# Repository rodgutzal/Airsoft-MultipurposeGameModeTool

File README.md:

# Airsoft-MultipurposeGameModeTool

Herramienta multipropósito para partidas de airsoft, con hardware y software propios. Un mismo dispositivo cubre cinco modos de juego: captura la bandera, control de zona, rey de la colina, desactivación de bomba y extracción de paquete.

## Estructura

| Carpeta | Contenido |
| --- | --- |
| `Hw` | Hardware: esquemático en KiCad, PDF, lista de materiales, asignación de pines y propuesta de PCB (`Hw/pcb`). |
| `Sw` | Firmware en ESP-IDF, con su documentación. |

## Estado

Hardware en versión 0.8, en [`Hw/esquematico_v1`](Hw/esquematico_v1/README.md). Usa un ESP32-S3-DevKitC-1 N16R8 con pantalla TFT de 3.5 pulgadas (480x320, bus paralelo de 16 bits y touch resistivo XPT2046 por SPI), un expansor I2C MCP23017 para el teclado 4x4, dos switches y un push button, dos tiras LED RGB direccionables WS2812B, y audio por I2S con un amplificador MAX98357A y una bocina de 4 Ω. La alimentación tiene dos opciones y se construye una sola: un módulo LUORNG V8 para dos celdas 18650 (opción A) o TP4056 con MT3608 discretos (opción B). Todas las entradas digitales tienen pull-up externo de 10k.

La opción C (v0.9, en [`Hw/esquematico_v1/opcion_c`](Hw/esquematico_v1/opcion_c/README.md)) quita los módulos comprados para armar todo en una PCB propia: módulo ESP32-S3-WROOM-1 N16R8 sin tarjeta de desarrollo, cargador TP4056 con protección DW01A y FS8205A, elevador TPS61022, regulador AP7361C, MAX98357A suelto y USB-C al USB nativo para grabar, depurar y cargar.

El firmware está en `Sw` (ESP-IDF). Hoy arranca, fija el CPU a 240 MHz, inicia la flash y un ciclo principal de 5 ms con un LED de heartbeat; pantalla, audio, tiras LED, teclado y entradas todavía no tienen driver, y nada se ha probado en la placa. Su pinout es el de v0.7 y falta migrarlo a v0.8 (ver [`Sw/MapaPines.md`](Sw/MapaPines.md)).

## Documentación

Dónde leer según lo que necesites:

| Si quieres... | Lee |
| --- | --- |
| Entender el hardware y su pinout | [`Hw/esquematico_v1/README.md`](Hw/esquematico_v1/README.md) |
| Ver la variante para PCB propia | [`Hw/esquematico_v1/opcion_c/README.md`](Hw/esquematico_v1/opcion_c/README.md) y [`Hw/pcb/pcb_propuesta_v0.3.md`](Hw/pcb/pcb_propuesta_v0.3.md) |
| Entender cómo está organizado el firmware | [`Sw/README.md`](Sw/README.md) |
| Trabajar en el firmware (reglas, flujo de Git, cómo agregar un driver) | [`Sw/GuiaDesarrollo.md`](Sw/GuiaDesarrollo.md) |
| Saber qué hace cada función de cada driver | [`Sw/ReferenciaApi.md`](Sw/ReferenciaApi.md) |
| Saber qué pin del micro hace qué | [`Sw/MapaPines.md`](Sw/MapaPines.md) |
| Conocer el diseño objetivo del firmware | [`Sw/Arquitectura.md`](Sw/Arquitectura.md) |
| Ver el uso de memoria y los warnings | [`Sw/MemoryUsage.md`](Sw/MemoryUsage.md) y [`Sw/Warnings.md`](Sw/Warnings.md) |

## Requisitos de diseño

La autonomía mínima es de 5 horas, en periodos de uso de unos 30 minutos. El audio debe oírse a 15 metros al aire libre. El microcontrolador debe poder comprarse fácilmente en México y los precios se calculan en pesos mexicanos.

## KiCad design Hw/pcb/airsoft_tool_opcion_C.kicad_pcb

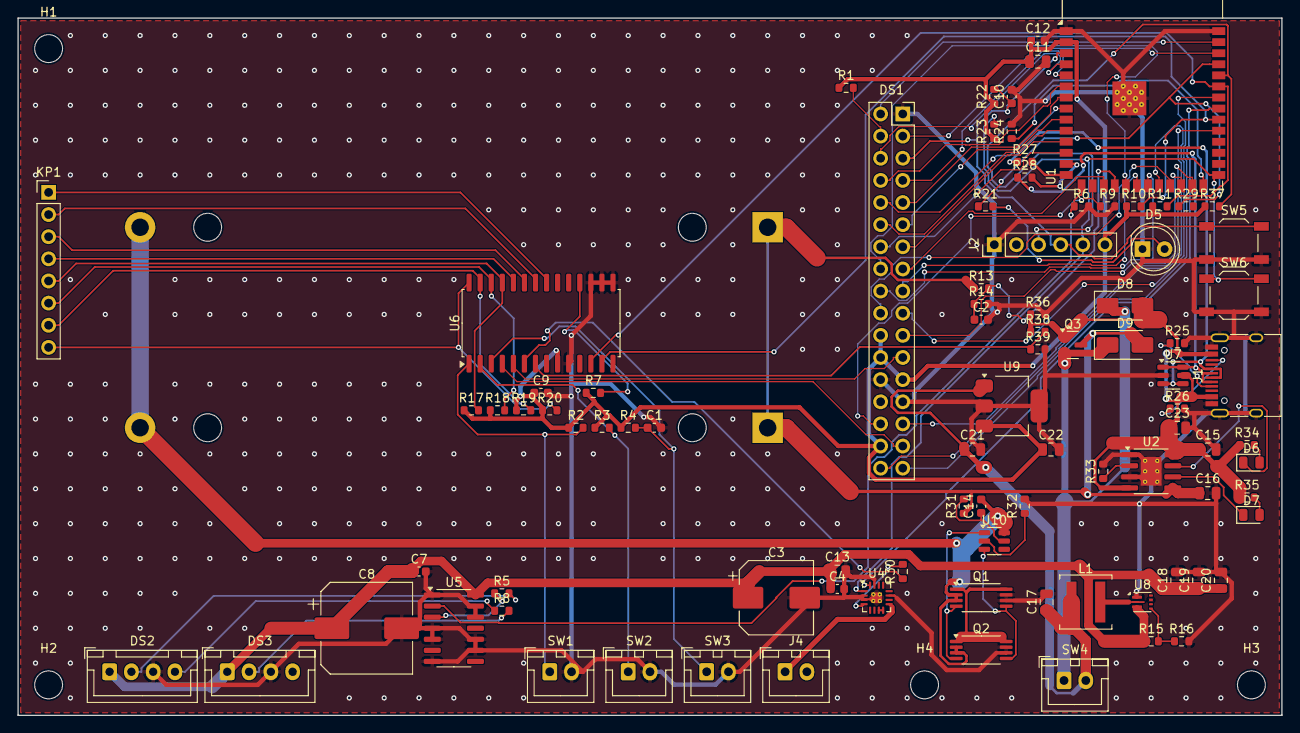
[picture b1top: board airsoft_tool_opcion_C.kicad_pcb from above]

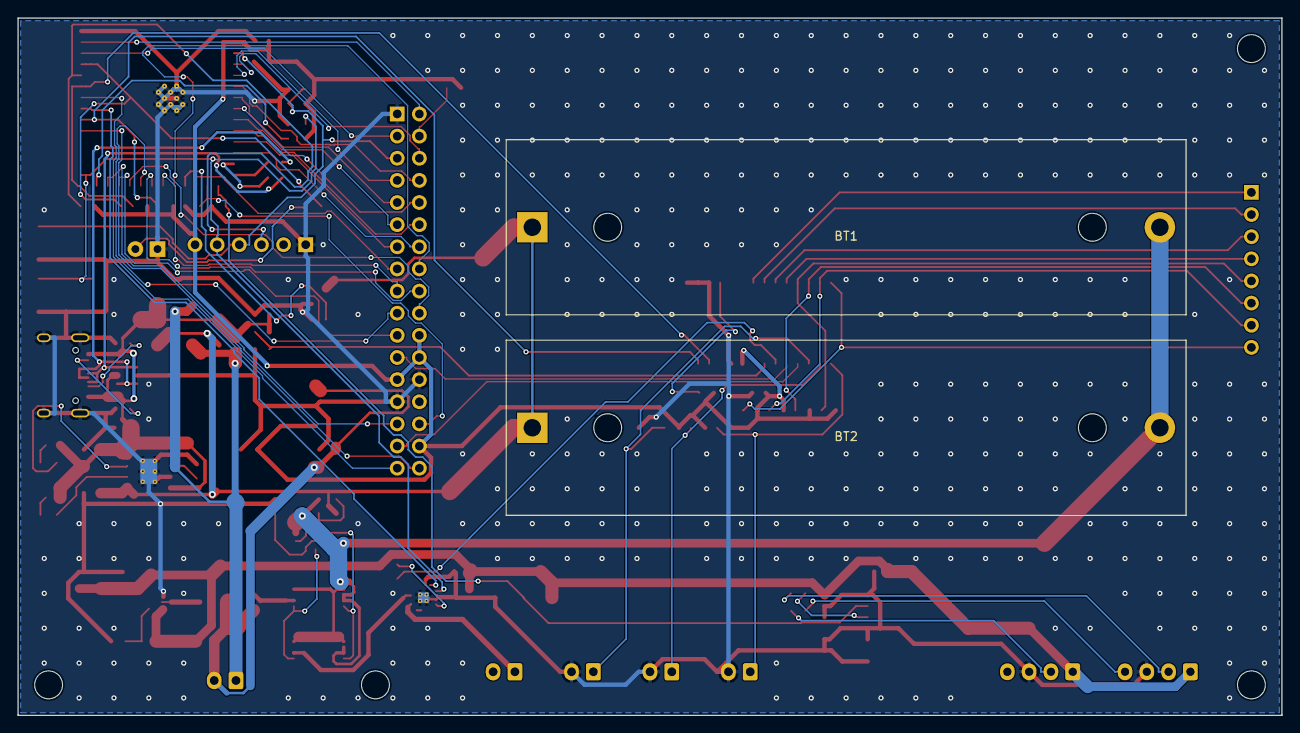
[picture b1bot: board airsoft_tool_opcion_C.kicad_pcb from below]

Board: 2 copper layers, 145.0 x 80.0 mm, 96 parts (2 on the bottom side), 84 nets.

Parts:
BT1, BT2: 18650; BatteryHolder_MPD_BH-18650-PC2
C1, C2, C4, C7, C9, C12, C14: 100nF; C_0603_1608Metric
C3: 470uF 10V; CP_Elec_8x10
C8: 1000uF; CP_Elec_10x10
C10: 1uF; C_0603_1608Metric
C11, C17, C18, C19, C20: 22uF; C_0805_2012Metric
C13, C15, C16, C21, C22, C23: 10uF; C_0805_2012Metric
D5: Verde 5 mm; LED_D5.0mm
D6: Rojo; LED_0805_2012Metric
D7: Verde; LED_0805_2012Metric
D8, D9: SS34; D_SMA
DS1: LCD 3.5in 480x320 ILI9486 2x17; PinSocket_2x17_P2.54mm_Vertical
DS2, DS3: Tira WS2812B 15 LEDs; JST_XH_B4B-XH-A_1x04_P2.50mm_Vertical
H1, H2, H3, H4: M3; MountingHole_3.2mm_M3
J1: USB-C 16P (USB 2.0); USB_C_Receptacle_HRO_TYPE-C-31-M-12
J2: UART0 / BOOT 1x6; PinHeader_1x06_P2.54mm_Vertical
J4: Bocina; JST_XH_B2B-XH-A_1x02_P2.50mm_Vertical
KP1: Teclado membrana 4x4; PinHeader_1x08_P2.54mm_Vertical
L1: 1uH Isat 8A; L_Coilcraft_XAL5030-XXX
Q1, Q2: FS8205A; TSSOP-8_4.4x3mm_P0.65mm
Q3: AO3401A; SOT-23
R1, R2, R3, R4, R7, R17, R18, R19, R20, R22, R23, R24, R36, R37: 10k; R_0603_1608Metric
R5, R8, R21: 330; R_0603_1608Metric
R6, R9, R13, R14, R39: 100k; R_0603_1608Metric
R10, R11: 4.7k; R_0603_1608Metric
R15: 750k 1%; R_0603_1608Metric
R16: 100k 1%; R_0603_1608Metric
R25, R26: 5.1k; R_0603_1608Metric
R27, R28: 22; R_0603_1608Metric
R29: 499; R_0603_1608Metric
R30: 634k 1%; R_0603_1608Metric
R31: 100; R_0603_1608Metric
R32, R34, R35: 1k; R_0603_1608Metric
R33: 1.2k; R_0603_1608Metric
R38: 47k; R_0603_1608Metric
SW1: Selector de equipo; JST_XH_B2B-XH-A_1x02_P2.50mm_Vertical
SW2: Armado de bomba (llave); JST_XH_B2B-XH-A_1x02_P2.50mm_Vertical
SW3: Push button de accion; JST_XH_B2B-XH-A_1x02_P2.50mm_Vertical
SW4: Encendido (3 A); JST_XH_B2B-XH-A_1x02_P2.50mm_Vertical
SW5: RESET; SW_SPST_TL3342
SW6: BOOT; SW_SPST_TL3342
U1: ESP32-S3-WROOM-1-N16R8; ESP32-S3-WROOM-1
U2: TP4056; SOIC-8-1EP_3.9x4.9mm_P1.27mm_EP2.41x3.3mm_ThermalVias
U4: MAX98357AETE+; TQFN-16-1EP_3x3mm_P0.5mm_EP1.23x1.23mm_ThermalVias
U5: 74AHCT125; SOIC-14_3.9x8.7mm_P1.27mm
U6: MCP23017-E/SP; SOIC-28W_7.5x17.9mm_P1.27mm
U7: USBLC6-2SC6; SOT-23-6
U8: TPS61022; Texas_RWU0007A_VQFN-7_2x2mm_P0.5mm
U9: AP7361C-33E; SOT-223-3_TabPin2
U10: DW01A; SOT-23-6

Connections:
/+3V3: C9.1, C11.1, C12.1, C22.1, DS1.22, DS1.24, DS1.25, DS1.32, J2.6, R1.1, R2.1, R3.1, R4.1, R7.1, R10.1, R11.1, R17.1, R18.1, R19.1, R20.1, R22.1, R23.1, R37.1, U1.2, U6.9, U9.3
/+5V: C3.1, C4.1, C7.1, C8.1, C13.1, C18.1, C19.1, C20.1, DS2.1, DS3.1, R15.1, U4.7, U4.8, U5.14, U8.3
/AMP_SD: R30.2, U4.4
/AMP_SD_CTRL: R30.1, U6.6
/BAT_NEG: BT1.2, BT2.2, C14.2, Q1.2, Q1.3, Q2.2, Q2.3, U10.6
/BOOST_SW: L1.2, U8.2
/BTN_ACCION: C1.1, R4.2, SW3.1, U6.3
/CHG_LED_G: D7.1, U2.6
/CHG_LED_GA: D7.2, R35.2
/CHG_LED_R: D6.1, U2.7
/CHG_LED_RA: D6.2, R34.2
/CHG_PROG: R33.1, U2.2
/DW_CS: R32.1, U10.2
/DW_VCC: C14.1, R31.2, U10.5
/ESP_EN: C10.1, DS1.5, J2.4, R22.2, SW5.1, U1.3
/EXP_RESET: R7.2, U6.18
/FB_5V: R15.2, R16.1, U8.4
/GND: C1.2, C2.2, C3.2, C4.2, C7.2, C8.2, C9.2, C10.2, C11.2, C12.2, C13.2, C15.2, C16.2, C17.2, C18.2, C19.2, C20.2, C21.2, C22.2, C23.2, D5.1, DS1.1, DS1.26, DS1.27, DS2.3, DS3.3, J1.A1, J1.A12, J1.B1, J1.B12, J1.S1, J2.1, Q1.6, Q1.7, Q2.6, Q2.7, R6.2, R9.2, R14.2, R16.2, R24.2, R25.2, R26.2, R32.2, R33.2, R36.2, R39.2, SW1.2, SW2.2, SW3.2, SW5.2, SW6.2, U1.1, U1.40, U1.41, U2.1, U2.3, U2.9, U4.2, U4.3, U4.11, U4.15, U4.17, U5.1, U5.4, U5.5, U5.7, U5.9, U5.10, U5.12, U5.13, U6.10, U6.15, U6.16, U6.17, U7.2, U8.1, U8.6, U9.2
/I2C_SCL: R11.2, U1.35, U6.12
/I2C_SDA: R10.2, U1.32, U6.13
/I2S_BCLK: U1.33, U4.16
/I2S_DIN: J2.5, R23.2, SW6.1, U1.27, U4.1
/I2S_LRC: R24.1, U1.26, U4.14
/KEY_C1: KP1.5, R17.2, U6.25
/KEY_C2: KP1.6, R18.2, U6.26
/KEY_C3: KP1.7, R19.2, U6.27
/KEY_C4: KP1.8, R20.2, U6.28
/KEY_F1: KP1.1, U6.21
/KEY_F2: KP1.2, U6.22
/KEY_F3: KP1.3, U6.23
/KEY_F4: KP1.4, U6.24
/LCD_BL: DS1.23, U6.5
/LCD_D0: DS1.6, U1.4
/LCD_D1: DS1.7, U1.5
/LCD_D2: DS1.8, U1.6
/LCD_D3: DS1.9, U1.7
/LCD_D4: DS1.10, U1.8
/LCD_D5: DS1.11, U1.9
/LCD_D6: DS1.12, U1.10
/LCD_D7: DS1.13, U1.11
/LCD_D8: DS1.14, U1.12
/LCD_D9: DS1.15, U1.17
/LCD_D10: DS1.16, U1.19
/LCD_D11: DS1.17, U1.20
/LCD_D12: DS1.18, U1.21
/LCD_D13: DS1.19, U1.22
/LCD_D14: DS1.20, U1.23
/LCD_D15: DS1.21, U1.24
/LCD_RD: DS1.4, R1.2
/LCD_RS: DS1.2, U1.39
/LCD_WR: DS1.3, U1.38
/LED_ESTADO: R21.1, R29.1, U1.37
/LED_ESTADO_A: D5.2, R21.2
/LED_TIRA: R6.1, U1.15, U5.2
/PROT_D: Q1.1, Q1.8, Q2.1, Q2.8
/PROT_OC: Q1.5, Q2.5, U10.3
/PROT_OD: Q1.4, Q2.4, U10.1
/SPK_N: J4.2, U4.10
/SPK_P: J4.1, U4.9
/SW_ARMADO: R3.2, SW2.1, U6.2
/SW_EQUIPO: R2.2, SW1.1, U6.1
/TIRA1_5V: R5.1, U5.3
/TIRA1_DIN: DS2.2, R5.2
/TIRA1_DOUT: DS2.4, R8.1
/TIRA2_DIN: DS3.2, R8.2
/TOUCH_CLK: DS1.34, U1.31
/TOUCH_CS: DS1.33, U1.34
/TOUCH_MISO: DS1.29, U1.25
/TOUCH_MOSI: DS1.30, R9.1, U1.16
/TOUCH_PEN: DS1.31, U6.4
/UART_RX0: J2.3, R37.2, U1.36
/UART_TX0: J2.2, R29.2
/USB_CC1: J1.A5, R25.1
/USB_CC2: J1.B5, R26.1
/USB_DN: J1.A7, J1.B7, R28.1, U7.1, U7.6
/USB_DN_MCU: R28.2, U1.13
/USB_DP: J1.A6, J1.B6, R27.1, U7.3, U7.4
/USB_DP_MCU: R27.2, U1.14
/USB_PRESENTE: R38.2, R39.1, U6.7
/VBAT_ADC: C2.1, R13.2, R14.1, U1.18
/VBAT_CELDA: BT1.1, BT2.1, C16.1, D9.2, Q3.3, R13.1, R31.1, U2.5
/VBUS_USB: C15.1, C23.1, D8.2, J1.A4, J1.A9, J1.B4, J1.B9, Q3.1, R34.1, R35.1, R36.1, R38.1, U2.4, U2.8, U7.5
/VSYS: D8.1, D9.1, Q3.2, SW4.1
/VSYS_SW: C17.1, C21.1, L1.1, SW4.2, U8.5, U8.7, U9.1

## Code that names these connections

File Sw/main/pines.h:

#pragma once

/* Asignación de pines. Fuente: Hw/esquematico_v1/README.md
 * No usar: GPIO19/20 (USB nativo), GPIO26-32 (flash), GPIO35-37 (PSRAM octal). */

/* Pantalla TFT, bus paralelo de 8 bits */
#define PIN_LCD_RS   1
#define PIN_LCD_WR   2
#define PIN_LCD_D0   4
#define PIN_LCD_D1   5
#define PIN_LCD_D2   6
#define PIN_LCD_D3   7
#define PIN_LCD_D4   15
#define PIN_LCD_D5   16
#define PIN_LCD_D6   17
#define PIN_LCD_D7   18
#define PIN_LCD_RST  41
#define PIN_LCD_CS   42

/* Teclado 4x4: filas salidas, columnas entradas con pull-up */
#define PIN_KEY_F1   11
#define PIN_KEY_F2   12
#define PIN_KEY_F3   13
#define PIN_KEY_F4   14
#define PIN_KEY_C1   8
#define PIN_KEY_C2   9
#define PIN_KEY_C3   38
#define PIN_KEY_C4   39

/* Entradas */
#define PIN_SW_EQUIPO   21  /* abierto = rojo */
#define PIN_SW_ARMADO   47  /* interruptor de llave */
#define PIN_BTN_ACCION  48  /* comparte línea con el LED RGB de la tarjeta */

/* LEDs */
#define PIN_LED_ROJO   3    /* pin de arranque */
#define PIN_LED_AZUL   46   /* pin de arranque, pull-down de 100k */

/* Audio I2S (MAX98357A) */
#define PIN_I2S_BCLK   40
#define PIN_I2S_LRC    45   /* pin de arranque */
#define PIN_I2S_DIN    0    /* pin de arranque (botón BOOT) */

/* Batería */
#define PIN_VBAT_ADC   10   /* divisor 1:2 */

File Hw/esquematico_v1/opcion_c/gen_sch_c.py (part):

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place(R, "R22", "10k", 78.74, YE - 3.81, {"1": "+3V3", "2": "ESP_EN"}, local=("2",))
place(C, "C10", "1uF", 68.58, YE + 3.81, {"1": "ESP_EN", "2": "GND"}, local=("1",))
place(PUSH, "SW5", "RESET", 27.94, YE, {"1": "ESP_EN", "2": "GND"}, rot=180, ref_at=H[0], val_at=H[1], local=("1",))
label("ESP_EN", (38.1, YE), "R")
# GPIO0 (I2S_DIN): R23 a 3V3 y SW6 (BOOT) a GND
YB = 67.31
wire("U1.27", (33.02, YB))
place(R, "R23", "10k", 55.88, YB - 3.81, {"1": "+3V3", "2": "I2S_DIN"}, local=("2",))
wire("R23.2", (55.88, YB))
place(PUSH, "SW6", "BOOT", 27.94, YB, {"1": "I2S_DIN", "2": "GND"}, rot=180, ref_at=H[0], val_at=H[1], local=("1",))
label("I2S_DIN", (38.1, YB), "R")
# GPIO3 (LED_TIRA): R6 a GND
YT = 74.93
place(R, "R6", "100k", 50.8, YT, {"1": "LED_TIRA", "2": "GND"}, local=("1",), rot=270, ref_at=HR["ref_at"], val_at=HR["val_at"])
wire("U1.15", "R6.1")
label("LED_TIRA", (66.04, YT), "R")
# GPIO43: R21 y D5 (LED de estado) al GND del bloque
place(R, "R21", "330", 165.1, 62.23, {"1": "LED_ESTADO", "2": "LED_ESTADO_A"}, local="*", **HR)
place(LED, "D5", "Verde 5 mm", 177.8, 62.23, {"1": "GND", "2": "LED_ESTADO_A"}, rot=180,
      ref_at=(0, -3.81, 1), val_at=(0, 3.81, 1), local="*")
wire("U1.37", "R21.1"); wire("R21.2", "D5.2"); wire("D5.1", (XG, 62.23))
label("LED_ESTADO", (133.35, 62.23), "R")
# I2C: pull-ups R10 y R11 a 3V3
place(R, "R10", "4.7k", 162.56, 82.55, {"1": "+3V3", "2": "I2C_SDA"}, local=("2",))
place(R, "R11", "4.7k", 175.26, 82.55, {"1": "+3V3", "2": "I2C_SCL"}, local=("2",))
wire("U1.32", (162.56, 90.17), "R10.2")
wire("U1.35", (175.26, 97.79), "R11.2")
label("I2C_SDA", (133.35, 90.17), "R"); label("I2C_SCL", (133.35, 97.79), "R")
# GPIO45 (I2S_LRC) y GPIO46 (TOUCH_MOSI): pull-downs R24 y R9 al GND del bloque
place(R, "R24", "10k", 175.26, 115.57, {"1": "I2S_LRC", "2": "GND"}, local="*")
place(R, "R9", "100k", 162.56, 115.57, {"1": "TOUCH_MOSI", "2": "GND"}, local="*")
wire("U1.26", (175.26, 100.33), "R24.1"); wire("R24.2", (175.26, YG))
wire("U1.16", (162.56, 102.87), "R9.1"); wire("R9.2", (162.56, YG))
label("I2S_LRC", (133.35, 100.33), "R"); label("TOUCH_MOSI", (133.35, 102.87), "R")
text("EN: R22 10k + C10 1uF (guia de diseno de Espressif). SW5 = RESET, SW6 = BOOT (GPIO0 a GND).", 13, 150)
text("GPIO0 (I2S_DIN): pull-up R23. GPIO45 (I2S_LRC): pull-down R24, flash a 3.3 V. GPIO46 (TOUCH_MOSI): R9 a GND.", 13, 153)
text("GPIO3 (LED_TIRA): R6 a GND. GPIO35, 36 y 37 son de la PSRAM octal de la N16R8: sin conectar.", 13, 156)
text("GPIO19/20 al USB-C (bloque USB). GPIO43 (U0TXD) maneja D5 y sale al header J2; GPIO44 (U0RXD) es RX de J2.", 13, 159)
text("C11 22uF y C12 100nF junto al pin 2 (3V3). EPAD (41) a GND. Zona libre de cobre bajo la antena.", 13, 162)
text("Pantalla en bus 8080 de 16 bits (LCD_CAM). Teclado, switches, boton, PEN, BL, SD del amplificador y deteccion de USB en U6.", 13, 165)
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# VBUS: sube y pasa por C23 hacia U7 (pin 5); CC1/CC2 con R25/R26 a GND
YV, YGU = 33.02, 40.64
wire("J1.A4", (242.57, Y("J1.A4")), (242.57, YV), (289.56, YV))
label("VBUS_USB", (247.65, YV), "R")
place(R, "R25", "5.1k", 250.19, YGU + 3.81, {"1": "USB_CC1", "2": "GND"}, rot=180, local="*")
place(R, "R26", "5.1k", 262.89, YGU + 3.81, {"1": "USB_CC2", "2": "GND"}, rot=180, local="*")
wire("J1.A5", (250.19, Y("J1.A5")), "R25.1")
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place(CONN6, "J2", "UART0 / BOOT 1x6", 365.76, 80.01,
      {"1": "GND", "2": "UART_TX0", "3": "UART_RX0", "4": "ESP_EN", "5": "I2S_DIN", "6": "+3V3"},
      ref_at=(0, -11.43, 1), val_at=(0, 11.43, 1), local=("2", "3", "6"))
place(R, "R29", "499", 330.2, Y("J2.2"), {"1": "LED_ESTADO", "2": "UART_TX0"}, local=("2",), rot=90,
      ref_at=(0, -5.08, 1), val_at=(0, -2.54, 1))
wire("R29.2", "J2.2")
place(R, "R37", "10k", 340.36, 83.82, {"1": "+3V3", "2": "UART_RX0"}, rot=180, local="*",
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wire("J2.3", (340.36, Y("J2.3")), "R37.2")
wire("J2.6", (340.36, Y("J2.6")), "R37.1")
wire((340.36, Y("J2.3")), (337.82, Y("J2.3")))
label("UART_RX0", (337.82, Y("J2.3")), "L")
wire((340.36, Y("J2.6")), (337.82, Y("J2.6")))
label("+3V3", (337.82, Y("J2.6")), "L")
text("CC1/CC2 con 5.1k (R25, R26): el cargador entrega 5 V. VBUS_USB carga la bateria y alimenta el equipo.", 208, 100)
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wire("BT1.1", (33.02, YVB), (33.02, Y("BT2.1")), "BT2.1")
wire("BT1.2", (17.78, YVB), (17.78, Y("BT2.2")), "BT2.2")
wire((33.02, YVB), (99.06, YVB))                       # VBAT_CELDA
label("VBAT_CELDA", (50.8, YVB), "R")
place(PROT, "U10", "DW01A", 60.96, 222.25, {"5": "DW_VCC", "6": "BAT_NEG", "2": "DW_CS", "1": "PROT_OD", "3": "PROT_OC", "4": None},
      local="*")
# R31 de VBAT al VCC de U10; C14 entre VCC (5) y GND (6) de U10
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place(R, "R14", "100k", 99.06, YVB + 11.43, {"1": "VBAT_ADC", "2": "GND"}, local="*")
place(C, "C2", "100nF", 111.76, YVB + 11.43, {"1": "VBAT_ADC", "2": "GND"}, local="*")
wire("R13.2", "C2.1", (116.84, Y("C2.1")))
label("VBAT_ADC", (116.84, Y("C2.1")), "U")
wire("R14.2", "C2.2")
stub((105.41, Y("C2.2")), "D", "GND", 2.54)

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XL, XR = X("U2.4"), X("U2.5")
YB2 = Y("U2.9") + 5.08                                   # tierra del cargador
wire((132.08, YU), (193.04, YU))                         # VBUS_USB
label("VBUS_USB", (132.08, YU), "R")
wire((XL - 5.08, YU), (XL - 5.08, Y("U2.4")), "U2.4")
wire("U2.8", (XL - 2.54, Y("U2.8")), (XL - 2.54, Y("U2.4")))
for n in ("1", "3", "9"):
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# C16 entre BAT (5) y GND; BAT a VBAT_CELDA
place(C, "C16", "10uF", XR + 5.08, Y("U2.5") + 3.81, {"1": "VBAT_CELDA", "2": "GND"}, local="*")
wire("U2.5", (199.39, Y("U2.5")))
label("VBAT_CELDA", (199.39, Y("U2.5")), "D")
wire("C16.2", (XR + 5.08, YB2))
# LEDs de estado: VBUS -> R34/R35 -> LED -> ~CHRG / ~STDBY
for i, (rr, dd, col, pin) in enumerate((("R34", "D6", "Rojo", "7"), ("R35", "D7", "Verde", "6"))):
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text("Reparto de carga y encendido", 212, 193, 1.5, True)
YBT, XVS = 241.3, 271.78
wire((213.36, YU), (260.35, YU))                         # VBUS_USB
label("VBUS_USB", (213.36, YU), "R")
place(SCHOT, "D8", "SS34", 264.16, YU, {"2": "VBUS_USB", "1": "VSYS"}, rot=180,
      ref_at=(0, -3.81, 1), val_at=(0, 3.81, 1), local="*")
wire("D8.1", (XVS, YU), (XVS, YBT))                      # VSYS
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place(R, "R36", "10k", 248.92, Y("Q3.1") + 3.81, {"1": "VBUS_USB", "2": "GND"}, local=("1",),
      ref_at=(-5.08, -1.27, 1), val_at=(-5.08, 1.27, 1))
wire((213.36, YBT), (260.35, YBT))                       # VBAT_CELDA
label("VBAT_CELDA", (213.36, YBT), "R")
wire("Q3.3", (X("Q3.3"), YBT))
place(SCHOT, "D9", "SS34", 264.16, YBT, {"2": "VBAT_CELDA", "1": "VSYS"}, rot=180,
      ref_at=(0, -3.81, 1), val_at=(0, 3.81, 1), local="*")
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place(SPST, "SW4", "Encendido (3 A)", 281.94, 220.98, {"1": "VSYS", "2": "VSYS_SW"}, ref_at=H[0], val_at=H[1], local="*")
wire((XVS, 220.98), "SW4.1")
wire("SW4.2", (294.64, 220.98), (294.64, 226.06))
label("VSYS_SW", (294.64, 226.06), "D")
# USB presente: R38/R39 desde VBUS hacia U6 GPB6
place(R, "R38", "47k", 223.52, YU + 3.81, {"1": "VBUS_USB", "2": "USB_PRESENTE"}, local="*",
      ref_at=(-5.08, -1.27, 1), val_at=(-5.08, 1.27, 1))
place(R, "R39", "100k", 223.52, YU + 11.43, {"1": "USB_PRESENTE", "2": "GND"}, local=("1",),
      ref_at=(-5.08, -1.27, 1), val_at=(-5.08, 1.27, 1))
wire("R38.2", (226.06, Y("R38.2")))
label("USB_PRESENTE", (226.06, Y("R38.2")), "R")

# ---- 5.1 V (TPS61022) y 3.3 V (AP7361C)
frame(305, 189, 390, 330)
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place(BOOST, "U8", "TPS61022", 340.36, 223.52,
      {"7": "VSYS_SW", "5": "VSYS_SW", "6": "GND", "1": "GND", "2": "BOOST_SW", "3": "+5V", "4": "FB_5V"},
      ref_at=(-10.16, -10.16, 1), val_at=(0, 12.7, 1), local="*")
place(IND, "L1", "1uH Isat 8A", 341.63, YS, {"1": "VSYS_SW", "2": "BOOST_SW"}, rot=90,
      ref_at=(0, -6.35, 1), val_at=(0, -3.81, 1), local="*")
wire((309.88, YS), "L1.1")                               # VSYS_SW
label("VSYS_SW", (309.88, YS), "U")
wire("U8.7", (X("U8.7"), YS))
wire("U8.2", (X("U8.2"), YS), "L1.2")
wire("U8.5", (325.12, Y("U8.5")), (325.12, YS))
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text("U2: R33 1.2k = 1 A de carga. D6 rojo = cargando, D7 verde = carga terminada. TEMP a GND (sin termistor).", 13, 339)
text("Con USB: VSYS sale de VBUS por D8 y Q3 se abre (gate en VBUS). Sin USB: R36 baja el gate y Q3 conecta la bateria a VSYS.", 13, 342)
text("SW4 corta VSYS (la carga sigue con SW4 apagado). U8: Vout = 0.6 V x (1 + R15/R16) = 5.1 V, MODE a GND (PFM a baja carga).", 13, 345)
text("U9 da 3.3 V a 1 A desde VSYS_SW. R13/R14: 4.2 V -> 2.1 V en GPIO10. R38/R39: USB presente a U6 GPB6 (3.4 V con 5 V).", 13, 348)

# ================================================================ NOTAS
text("Opcion C (v0.9): todo discreto para PCB propia. Sin modulos comprados: ni DevKit, ni LUORNG V8, ni tarjeta MAX98357A.", 13, 362, 1.5, True)
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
